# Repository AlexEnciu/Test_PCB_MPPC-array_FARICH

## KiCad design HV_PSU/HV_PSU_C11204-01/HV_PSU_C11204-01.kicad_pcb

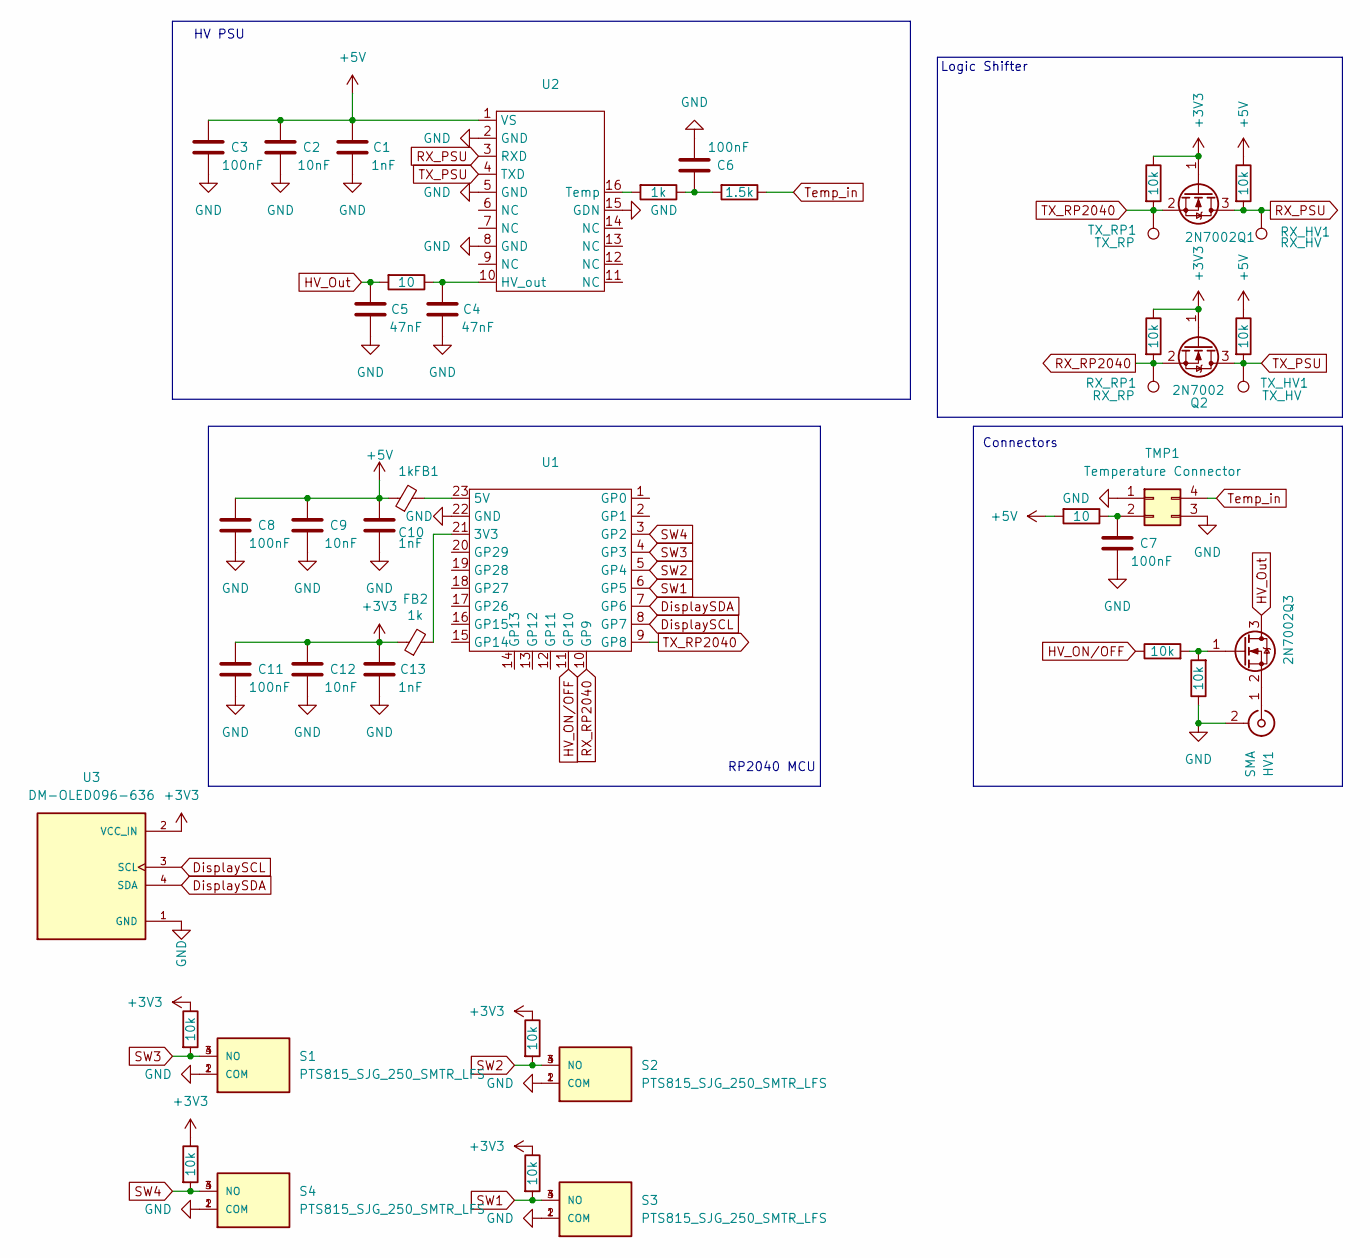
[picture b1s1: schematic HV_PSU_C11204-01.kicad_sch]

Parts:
C1, C10, C13: 1nF; C_0603_1608Metric
C2, C9, C12: 10nF; C_0603_1608Metric
C3, C6, C7, C8, C11: 100nF; C_0603_1608Metric
C4, C5: 47nF; C_0603_1608Metric
FB1, FB2: 1k; L_0603_1608Metric
HV1: SMA; SMA_Wurth_60312002114503_Vertical
Q1, Q2, Q3: 2N7002; SOT-23
R1, R2, R3, R4, R9, R10, R11, R12, R13, R14: 10k; R_0603_1608Metric
R5, R8: 10; R_0603_1608Metric
R6: 1k; R_0603_1608Metric
R7: 1.5k; R_0603_1608Metric
RX_HV1: RX_HV; TestPoint_Pad_D2.0mm
RX_RP1: RX_RP; TestPoint_Pad_D2.0mm
S1, S2, S3, S4: PTS815_SJG_250_SMTR_LFS; PTS815SJG250SMTRLFS; MOUSER_PART_NUMBER 611-PTS815SJG250SMTR
TMP1: Temperature Connector; PinSocket_2x02_P2.00mm_Vertical_SMD
TX_HV1: TX_HV; TestPoint_Pad_D2.0mm
TX_RP1: TX_RP; TestPoint_Pad_D2.0mm
U1: SuperMiniRP2040
U2: C11204-01
U3: DM-OLED096-636; MODULE_DM-OLED096-636; PARTREV 2018-09-10

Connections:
+3V3: C11.1, C12.1, C13.1, FB2.1, Q1.1 (G), Q2.1 (G), R1.1, R3.1, R9.1, R10.1, R11.1, R12.1, U3.2 (VCC_IN)
+5V: C1.1, C2.1, C3.1, C8.1, C9.1, C10.1, FB1.1, R2.1, R4.1, R8.2, U2.1 (VS)
DisplaySCL: U1.8 (GP7), U3.3 (SCL)
DisplaySDA: U1.7 (GP6), U3.4 (SDA)
GND: C1.2, C2.2, C3.2, C4.2, C5.2, C6.2, C7.2, C8.2, C9.2, C10.2, C11.2, C12.2, C13.2, HV1.2 (Ext), R14.1, S1.1 (COM), S1.2 (COM), S2.1 (COM), S2.2 (COM), S3.1 (COM), S3.2 (COM), S4.1 (COM), S4.2 (COM), TMP1.1, TMP1.3, U1.22 (GND), U2.2 (GND), U2.5 (GND), U2.8 (GND), U2.15 (GDN), U3.1 (GND)
HV_ON/OFF: R13.1, U1.11 (GP10)
HV_Out: C5.1, Q3.3 (D), R5.2
unnamed: C6.1, R6.1, R7.2
unnamed: HV1.1 (In), Q3.2 (S)
unnamed: Q3.1 (G), R13.2, R14.2
unnamed: C7.1, R8.1, TMP1.2
unnamed: FB2.2, U1.21 (3V3)
unnamed: FB1.2, U1.23 (5V)
unnamed: C4.1, R5.1, U2.10 (HV_out)
unnamed: R6.2, U2.16 (Temp)
RX_PSU: Q1.3 (D), R2.2, RX_HV1.1, U2.3 (RXD)
RX_RP2040: Q2.2 (S), R3.2, RX_RP1.1, U1.10 (GP9)
SW1: R12.2, S3.3 (NO), S3.4 (NO), U1.6 (GP5)
SW2: R11.2, S2.3 (NO), S2.4 (NO), U1.5 (GP4)
SW3: R10.2, S1.3 (NO), S1.4 (NO), U1.4 (GP3)
SW4: R9.2, S4.3 (NO), S4.4 (NO), U1.3 (GP2)
TX_PSU: Q2.3 (D), R4.2, TX_HV1.1, U2.4 (TXD)
TX_RP2040: Q1.2 (S), R1.2, TX_RP1.1, U1.9 (GP8)
Temp_in: R7.1, TMP1.4

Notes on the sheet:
Connectors
Logic Shifter
HV PSU
RP2040 MCU

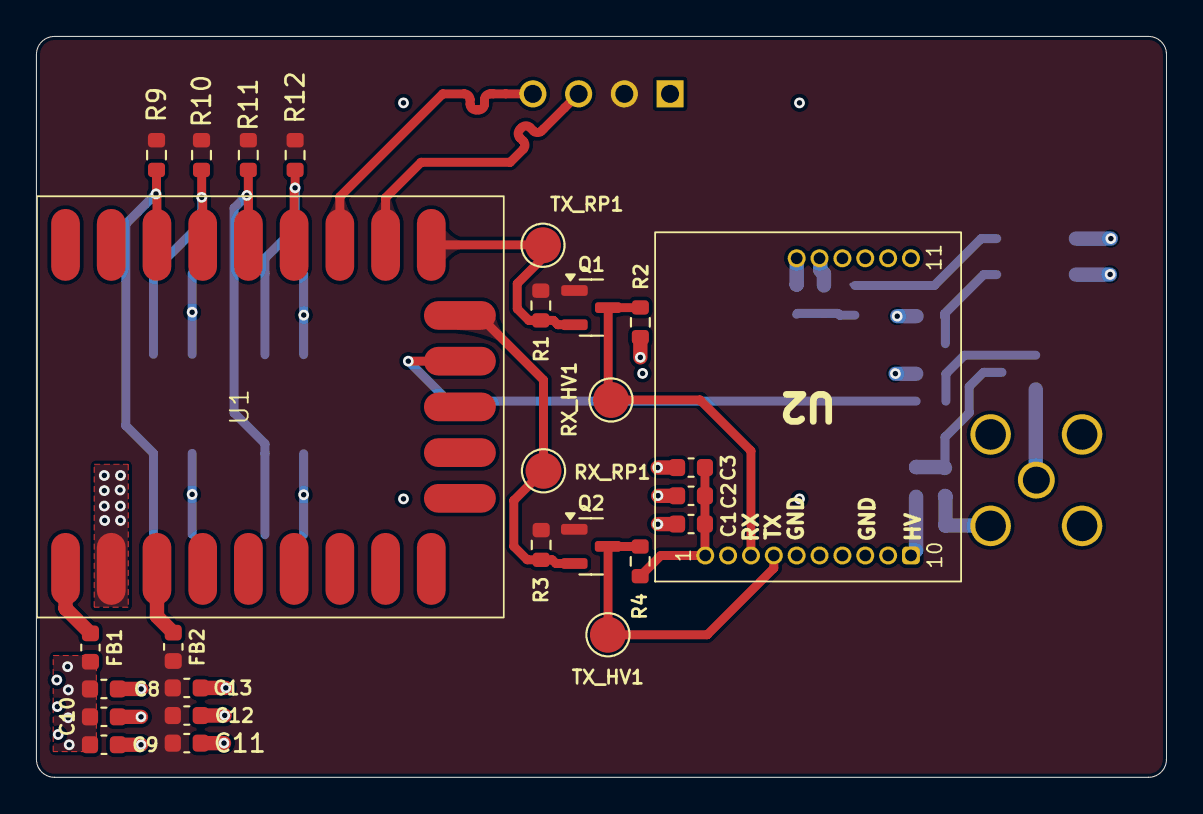
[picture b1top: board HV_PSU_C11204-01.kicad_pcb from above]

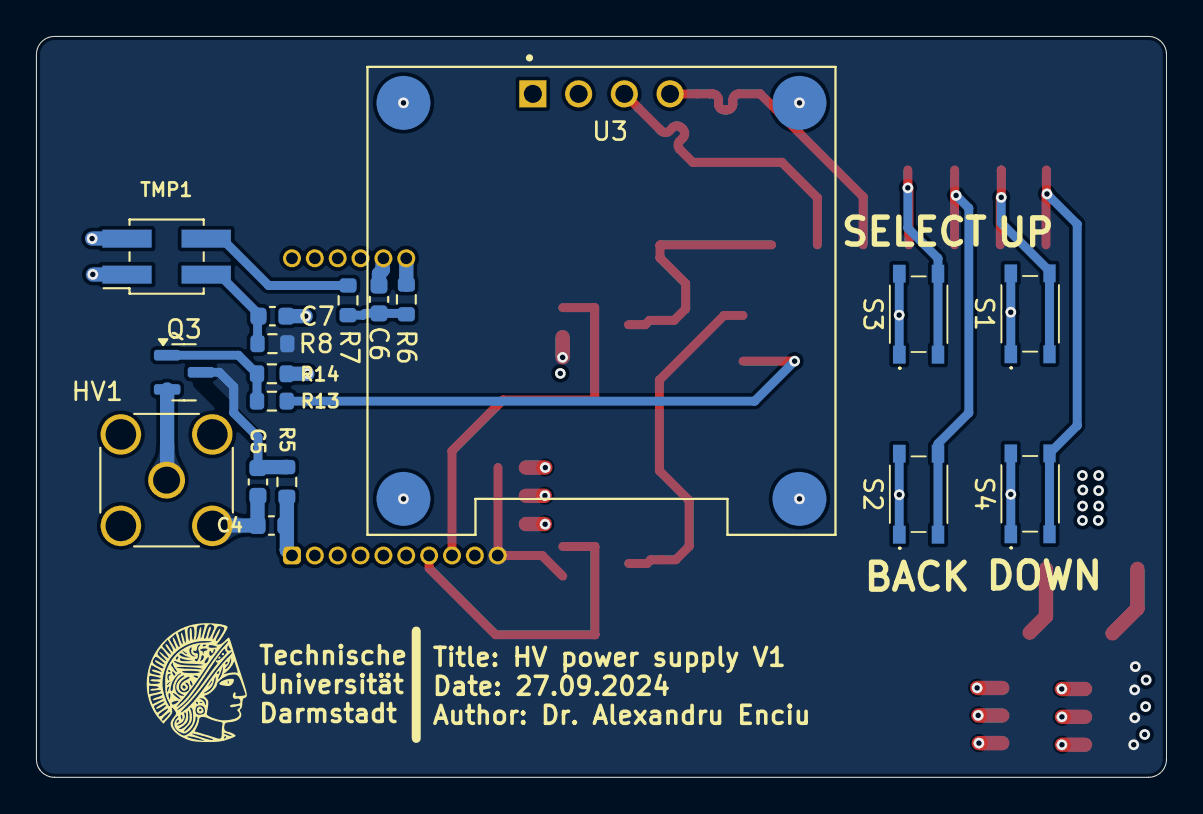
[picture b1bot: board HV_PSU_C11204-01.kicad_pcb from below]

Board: 4 copper layers, 62.8 x 41.2 mm, 45 parts (18 on the bottom side), 24 nets.
